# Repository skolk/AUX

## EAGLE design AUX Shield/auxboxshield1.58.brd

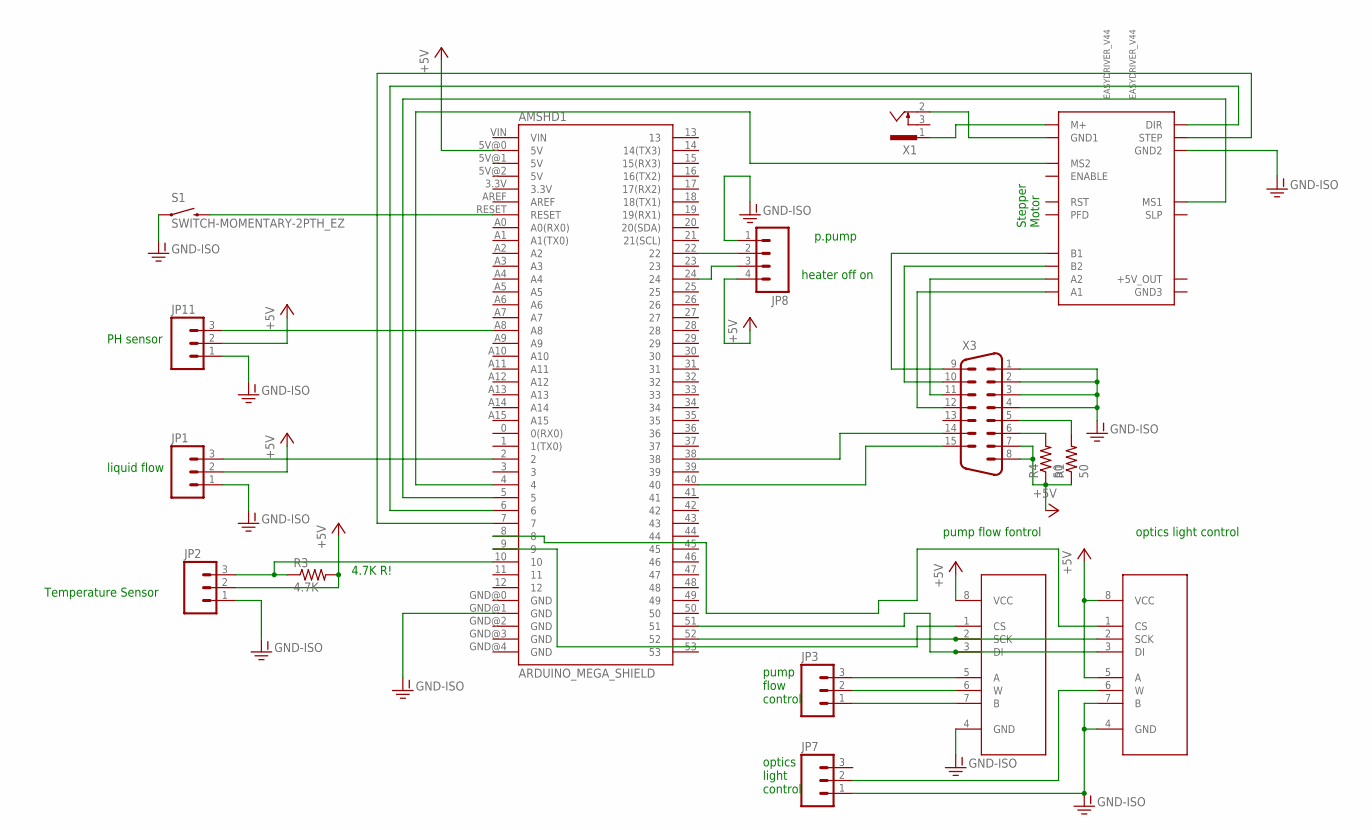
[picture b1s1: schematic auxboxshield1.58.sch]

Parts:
AMSHD1: ARDUINO_MEGA_SHIELD
EASYDRIVER_V44: EASYDRIVER_V44
JP1, JP2, JP3, JP7, JP11: M03POLAR; MOLEX-1X3
JP8: M04POLAR; MOLEX-1X4
R1, R4: 50; AXIAL-0.3
R3: 4.7K; AXIAL-0.3
S1: SWITCH-MOMENTARY-2PTH_EZ; TACTILE-PTH-EZ
U1, U2: MCP41XXXDIL; DIL-08
X1: SCD-014A; SCD-014-A
X3: M15V

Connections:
+5V: AMSHD1.5V@0 (5V), JP1.2, JP2.2, JP8.4, JP11.2, R1.P$1 (1), R3.P$2 (2), R4.P$1 (1), U1.5 (A), U1.8 (VCC), U2.8 (VCC), X3.7, X3.8
GND-ISO: AMSHD1.GND@1 (GND), EASYDRIVER_V44.GND2, JP1.1, JP2.1, JP7.1, JP8.1, JP11.1, S1.1, U1.4 (GND), U1.7 (B), U2.4 (GND), X3.1, X3.2, X3.3, X3.4
unnamed: EASYDRIVER_V44.M+, X1.1
unnamed: AMSHD1.38, X3.14
unnamed: R1.P$2 (2), X3.5
unnamed: EASYDRIVER_V44.GND1, X1.2
unnamed: EASYDRIVER_V44.A1, X3.12
unnamed: AMSHD1.RESET, S1.3 (2)
unnamed: EASYDRIVER_V44.A2, X3.11
unnamed: AMSHD1.9, U2.1 (CS)
unnamed: AMSHD1.5, EASYDRIVER_V44.MS1
unnamed: AMSHD1.22, JP8.2
unnamed: AMSHD1.A8, JP11.3
unnamed: AMSHD1.4, EASYDRIVER_V44.MS2
unnamed: AMSHD1.52, U1.2 (SCK), U2.2 (SCK)
unnamed: AMSHD1.24, JP8.3
unnamed: AMSHD1.40, X3.15
unnamed: AMSHD1.51, U1.3 (DI), U2.3 (DI)
unnamed: JP3.3, U2.5 (A)
unnamed: JP3.2, U2.6 (W)
unnamed: AMSHD1.10, JP2.3, R3.P$1 (1)
unnamed: EASYDRIVER_V44.B2, X3.10
unnamed: AMSHD1.2, JP1.3
unnamed: AMSHD1.6, EASYDRIVER_V44.DIR
unnamed: AMSHD1.7, EASYDRIVER_V44.STEP
unnamed: EASYDRIVER_V44.B1, X3.9
unnamed: JP3.1, U2.7 (B)
unnamed: R4.P$2 (2), X3.6
unnamed: AMSHD1.8, U1.1 (CS)
unnamed: JP7.2, U1.6 (W)

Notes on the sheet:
Stepper Motor
Temperature Sensor
liquid flow
PH sensor
4.7K R!
pump flow fontrol
optics light control
heater off on
p.pump
pump flow control
optics light control

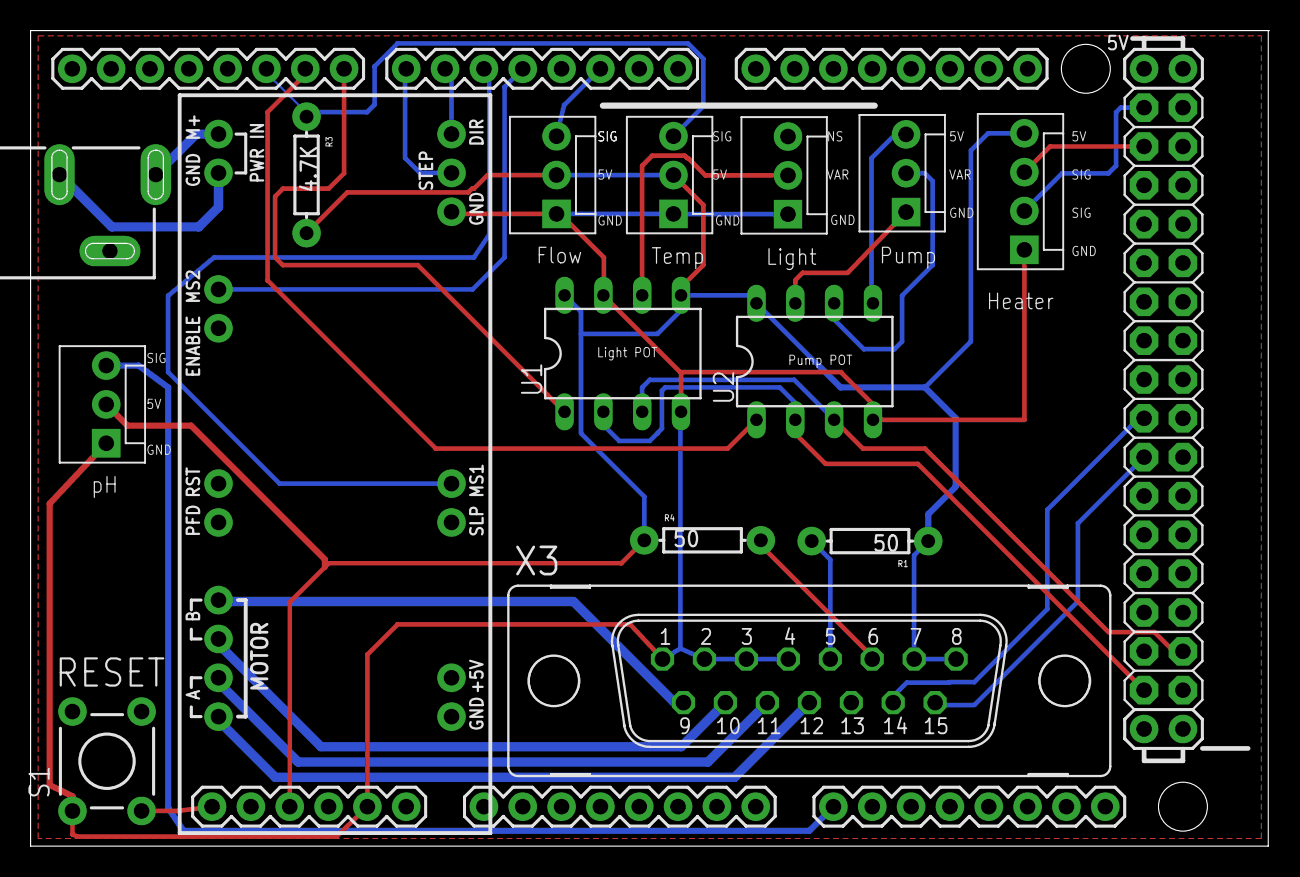
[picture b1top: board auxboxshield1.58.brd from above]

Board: 2 copper layers, 81.0 x 53.3 mm, 16 parts (0 on the bottom side), 30 nets.

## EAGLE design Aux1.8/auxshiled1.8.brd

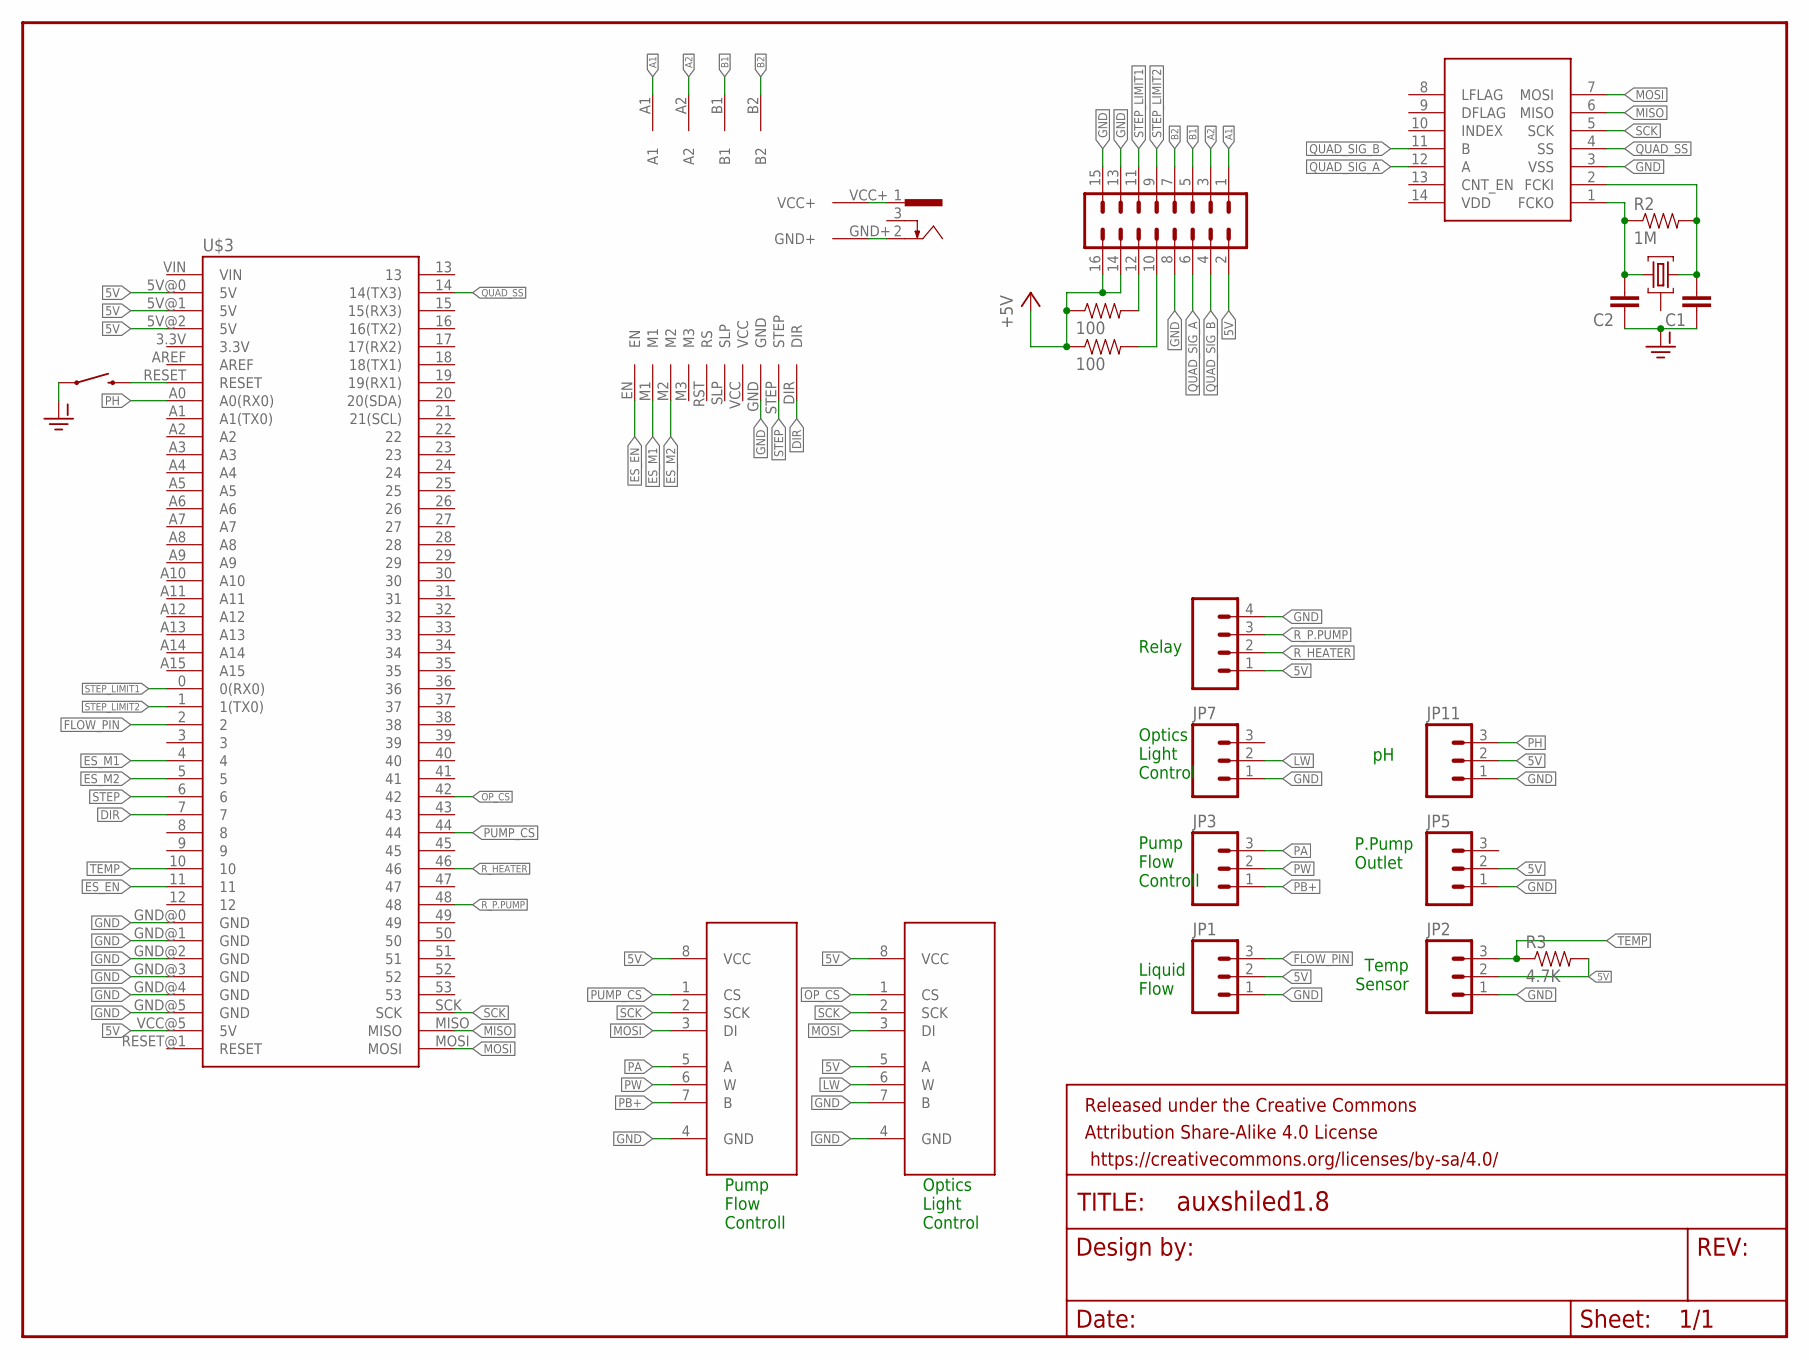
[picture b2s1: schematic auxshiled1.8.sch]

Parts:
C1, C2: 0.1UF-50V-20%(PTH)KIT-EZ; CAP-PTH-SMALL-KIT
FRAME1: FRAME-LETTER; CREATIVE_COMMONS
JP1, JP2, JP3, JP5, JP7, JP11: M03POLAR; MOLEX-1X3
PUMPDIGIPOT: MCP41XXXDIL; DIL-08
QF2: 14M20BHC49T; HC49U
R1, R4: 100; AXIAL-0.3
R2: 1M; AXIAL-0.3
R3: 4.7K; AXIAL-0.3
RELAY: M04POLAR; MOLEX-1X4
S1: SWITCH-MOMENTARY-2PTH_EZ; TACTILE-PTH-EZ
U1: MCP41XXXDIL; DIL-08
U$1: M08X2; 2X8
U$2: LS7366R; SO014
U$3: ARDUINO-MEGA-V2; ARDUINO_MEGA-PRO-5V
U$4: BIG_EASY_DRIVER; BIG_EASY_DRIVER_PACK
X1: SCD-014A; SCD-014-A

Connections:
5V: JP1.2, JP2.2, JP5.2, JP11.2, PUMPDIGIPOT.8 (VCC), R1.P$1 (1), R3.P$2 (2), R4.P$1 (1), RELAY.1, U1.5 (A), U1.8 (VCC), U$1.2, U$1.14, U$1.16, U$3.5V@0 (5V), U$3.5V@1 (5V), U$3.5V@2 (5V), U$3.VCC@5 (5V)
A1: U$1.1, U$4.A1
A2: U$1.3, U$4.A2
B1: U$1.5, U$4.B1
B2: U$1.7, U$4.B2
DIR: U$3.7, U$4.DIR
ES_EN: U$3.11, U$4.EN
ES_M1: U$3.4, U$4.M1
ES_M2: U$3.5, U$4.M2
FLOW_PIN: JP1.3, U$3.2
GND: C1.1, C2.1, JP1.1, JP2.1, JP5.1, JP7.1, JP11.1, PUMPDIGIPOT.4 (GND), RELAY.4, S1.1, U1.4 (GND), U1.7 (B), U$1.8, U$1.13, U$1.15, U$2.3 (VSS), U$3.GND@0 (GND), U$3.GND@1 (GND), U$3.GND@2 (GND), U$3.GND@3 (GND), U$3.GND@4 (GND), U$3.GND@5 (GND), U$4.GND
LW: JP7.2, U1.6 (W)
MISO: U$2.6 (MISO), U$3.MISO
MOSI: PUMPDIGIPOT.3 (DI), U1.3 (DI), U$2.7 (MOSI), U$3.MOSI
unnamed: U$4.VCC+, X1.1
unnamed: U$4.GND+, X1.2
unnamed: R1.P$2 (2), U$1.10
unnamed: S1.3 (2), U$3.RESET
unnamed: C1.2, QF2.3, R2.P$2 (2), U$2.2 (FCKI)
unnamed: C2.2, QF2.1, R2.P$1 (1), U$2.1 (FCKO)
unnamed: R4.P$2 (2), U$1.12
OP_CS: U1.1 (CS), U$3.42
PA: JP3.3, PUMPDIGIPOT.5 (A)
PB+: JP3.1, PUMPDIGIPOT.7 (B)
PH: JP11.3, U$3.A0 (A0(RX0))
PUMP_CS: PUMPDIGIPOT.1 (CS), U$3.44
PW: JP3.2, PUMPDIGIPOT.6 (W)
QUAD_SIG_A: U$1.6, U$2.12 (A)
QUAD_SIG_B: U$1.4, U$2.11 (B)
QUAD_SS: U$2.4 (SS), U$3.14 (14(TX3))
R_HEATER: RELAY.2, U$3.46
R_P.PUMP: RELAY.3, U$3.48
SCK: PUMPDIGIPOT.2 (SCK), U1.2 (SCK), U$2.5 (SCK), U$3.SCK
STEP: U$3.6, U$4.STEP
STEP_LIMIT1: U$1.11, U$3.0 (0(RX0))
STEP_LIMIT2: U$1.9, U$3.1 (1(TX0))
TEMP: JP2.3, R3.P$1 (1), U$3.10

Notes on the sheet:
Temp Sensor
Liquid Flow
Pump Flow Controll
Optics Light Control
Optics Light Control
P.Pump Outlet
Relay

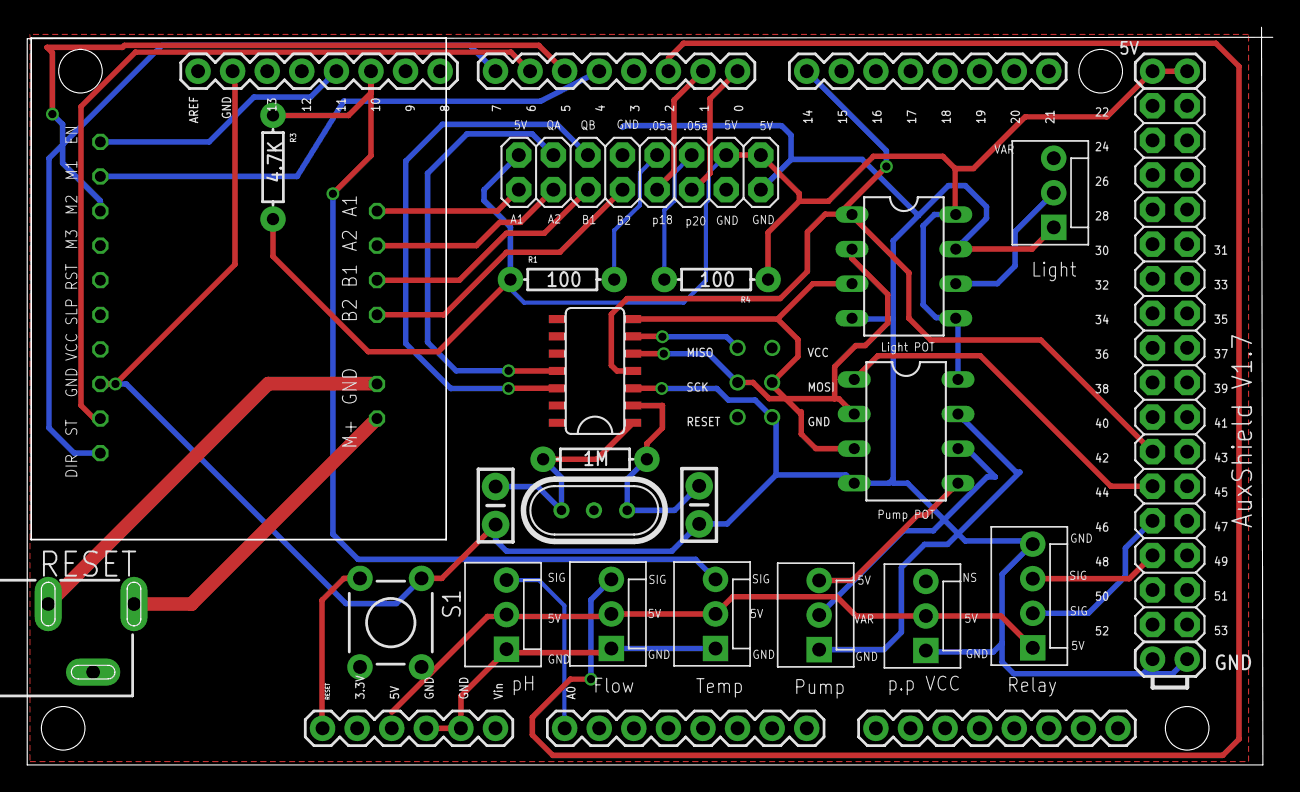
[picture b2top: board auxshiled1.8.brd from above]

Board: 2 copper layers, 91.3 x 54.1 mm, 23 parts (0 on the bottom side), 37 nets.

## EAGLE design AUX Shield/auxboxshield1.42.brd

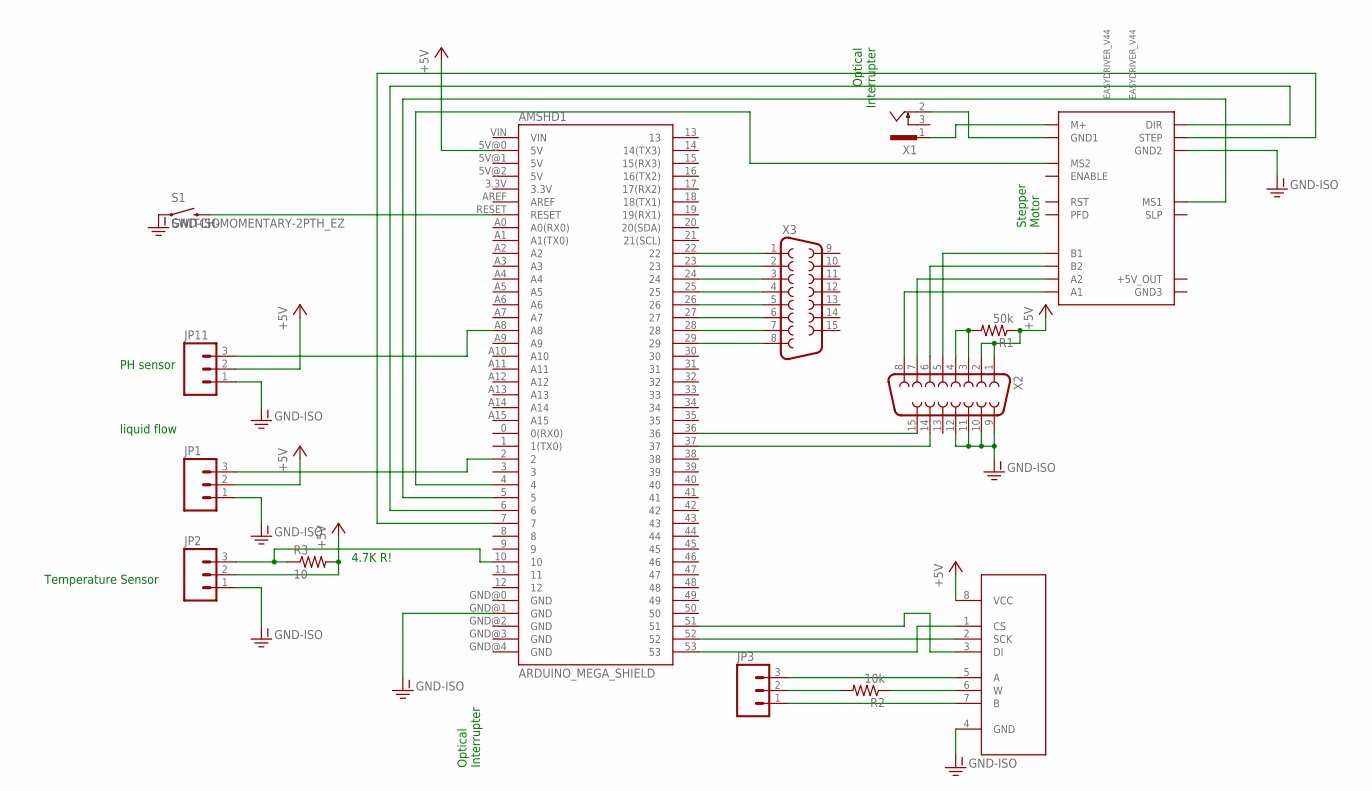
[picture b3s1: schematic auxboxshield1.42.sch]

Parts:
AMSHD1: ARDUINO_MEGA_SHIELD
EASYDRIVER_V44: EASYDRIVER_V44
JP1, JP2, JP3, JP11: M03POLAR; MOLEX-1X3
R1: 50k; AXIAL-0.3
R2: 10k; AXIAL-0.3
R3: 10; AXIAL-0.3
S1: SWITCH-MOMENTARY-2PTH_EZ; TACTILE-PTH-EZ
U2: MCP41XXXDIL; DIL-08
X1: SCD-014A; SCD-014-A
X2, X3: F15HP

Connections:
+5V: AMSHD1.5V@0 (5V), JP1.2, JP2.2, JP11.2, R1.P$1 (1), R3.P$2 (2), U2.8 (VCC), X2.1, X2.2
GND-ISO: AMSHD1.GND@1 (GND), EASYDRIVER_V44.GND2, JP1.1, JP2.1, JP11.1, S1.1, U2.4 (GND), X2.9, X2.10, X2.11, X2.12
unnamed: EASYDRIVER_V44.M+, X1.1
unnamed: EASYDRIVER_V44.A1, X2.8
unnamed: EASYDRIVER_V44.A2, X2.7
unnamed: R1.P$2 (2), X2.3, X2.4
unnamed: AMSHD1.22, X3.1
unnamed: EASYDRIVER_V44.GND1, X1.2
unnamed: EASYDRIVER_V44.B2, X2.6
unnamed: AMSHD1.23, X3.2
unnamed: AMSHD1.RESET, S1.3 (2)
unnamed: AMSHD1.24, X3.3
unnamed: EASYDRIVER_V44.B1, X2.5
unnamed: AMSHD1.53, U2.1 (CS)
unnamed: AMSHD1.5, EASYDRIVER_V44.MS1
unnamed: AMSHD1.25, X3.4
unnamed: AMSHD1.A8, JP11.3
unnamed: AMSHD1.4, EASYDRIVER_V44.MS2
unnamed: AMSHD1.52, U2.2 (SCK)
unnamed: AMSHD1.26, X3.5
unnamed: AMSHD1.27, X3.6
unnamed: AMSHD1.51, U2.3 (DI)
unnamed: JP3.3, U2.5 (A)
unnamed: AMSHD1.28, X3.7
unnamed: AMSHD1.29, X3.8
unnamed: R2.P$1 (1), U2.6 (W)
unnamed: JP3.2, R2.P$2 (2)
unnamed: AMSHD1.10, JP2.3, R3.P$1 (1)
unnamed: AMSHD1.2, JP1.3
unnamed: AMSHD1.6, EASYDRIVER_V44.DIR
unnamed: AMSHD1.7, EASYDRIVER_V44.STEP
unnamed: JP3.1, U2.7 (B)
unnamed: AMSHD1.36, X2.15
unnamed: AMSHD1.37, X2.14

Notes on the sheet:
Stepper Motor
Optical Interrupter
Temperature Sensor
liquid flow
PH sensor
4.7K R!

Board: 2 copper layers, 15 parts (0 on the bottom side), 34 nets, no tracks yet.

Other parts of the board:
DRILEGEND: DRILEGEND

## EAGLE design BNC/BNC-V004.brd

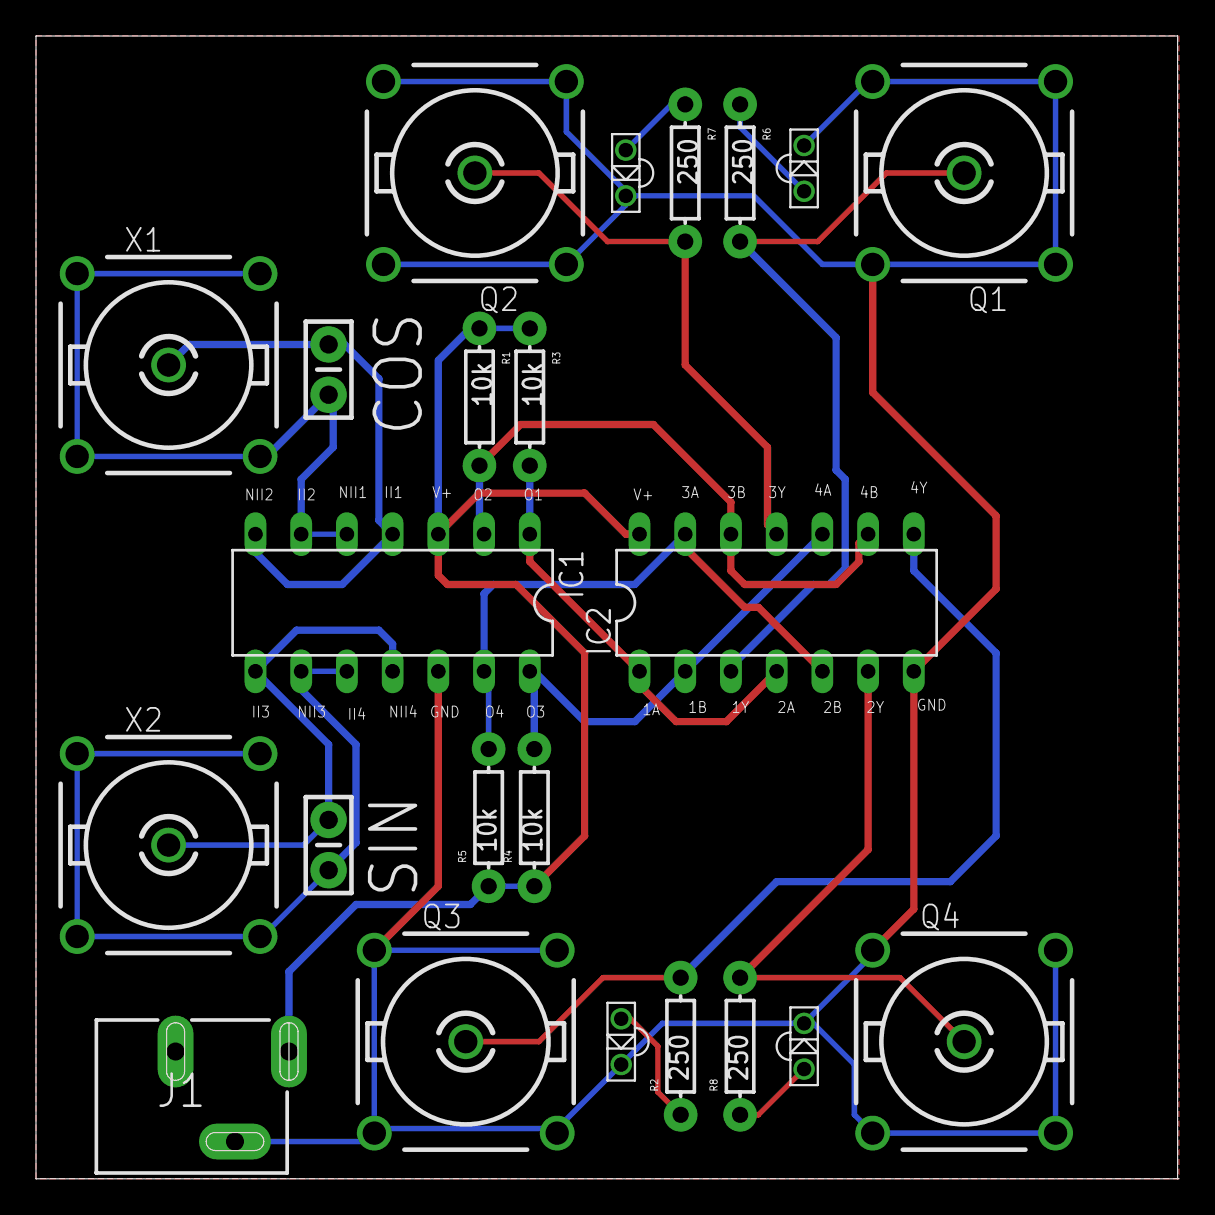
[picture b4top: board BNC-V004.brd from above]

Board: 2 copper layers, 63.5 x 63.5 mm, 23 parts (0 on the bottom side), 18 nets.

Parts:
C1, C3: CAP-PTH-SMALL-KIT
IAG2-D2, IAG3-D3, IAG4-D4: LTE-302
IAG-D1: LTE-302
IC1: LM339N; DIL14
IC2: 74AC08N; DIL14
J1: POWER_JACKSLT; POWER_JACK_SLOT
Q1, Q2, Q3, Q4: R141426
R1, R3, R4, R5: 10k; AXIAL-0.3
R2, R6, R7, R8: 250; AXIAL-0.3
X1, X2: R141426

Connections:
5V: IC1.3, IC2.14, J1.PWR, R1.P$1, R3.P$1, R4.P$1, R5.P$1
GND: IAG2-D2.C, IAG3-D3.C, IAG4-D4.C, IAG-D1.C, IC1.12, IC2.7, J1.GND@2, Q1.2, Q1.3, Q1.4, Q1.5, Q2.2, Q2.3, Q2.4, Q2.5, Q3.2, Q3.3, Q3.4, Q3.5, Q4.2, Q4.3, Q4.4, Q4.5
unnamed: IC1.2, IC2.9, IC2.12, R1.P$2
unnamed: IC2.11, Q2.1, R7.P$2
unnamed: IAG4-D4.A, R7.P$1
unnamed: IC1.1, IC2.1, IC2.4, R3.P$2
unnamed: IC1.14, IC2.2, IC2.10, R4.P$2
unnamed: IC1.13, IC2.5, IC2.13, R5.P$2
unnamed: C3.2, IC1.5, IC1.6, X1.2, X1.3, X1.4, X1.5
unnamed: C3.1, IC1.4, IC1.7, X1.1
unnamed: C1.1, IC1.8, IC1.11, X2.1
unnamed: C1.2, IC1.9, IC1.10, X2.2, X2.3, X2.4, X2.5
unnamed: IC2.8, Q3.1, R2.P$2
unnamed: IAG3-D3.A, R2.P$1
unnamed: IC2.6, Q4.1, R8.P$2
unnamed: IAG2-D2.A, R8.P$1
unnamed: IC2.3, Q1.1, R6.P$2
unnamed: IAG-D1.A, R6.P$1

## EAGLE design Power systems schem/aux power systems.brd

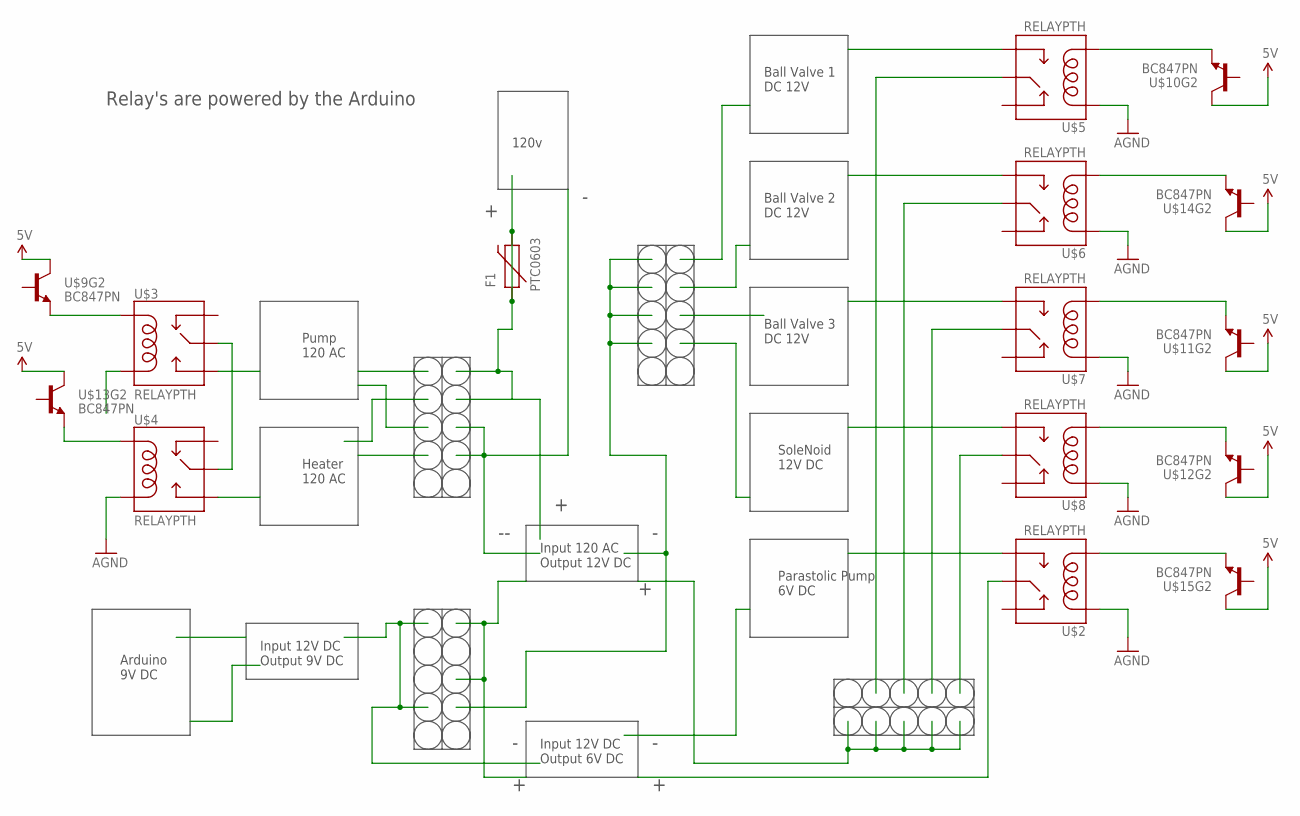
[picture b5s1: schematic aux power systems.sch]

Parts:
F1: PTC0603; 0603
U$2, U$3, U$4, U$5, U$6, U$7, U$8: RELAYPTH; RELAY-G5Q
U$9, U$10, U$11, U$12, U$13, U$14, U$15: BC847PN; SOT363

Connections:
5V: U$9.3 (C), U$10.3 (C), U$11.3 (C), U$12.3 (C), U$13.3 (C), U$14.3 (C), U$15.3 (C)
AGND: U$2.5 (COIL1), U$4.1 (COIL2), U$5.5 (COIL1), U$6.5 (COIL1), U$7.5 (COIL1), U$8.5 (COIL1)
B$2: U$2.3 (NO), U$3.3 (NO), U$4.3 (NO), U$5.3 (NO), U$6.3 (NO), U$7.3 (NO), U$8.3 (NO)
B$3: U$2.2 (MAIN), U$7.2 (MAIN)
unnamed: U$3.5 (COIL1), U$9.4 (E)
unnamed: U$4.5 (COIL1), U$13.4 (E)
unnamed: U$2.1 (COIL2), U$15.4 (E)
unnamed: U$8.1 (COIL2), U$12.4 (E)
unnamed: U$7.1 (COIL2), U$11.4 (E)
unnamed: U$6.1 (COIL2), U$14.4 (E)
unnamed: U$5.1 (COIL2), U$10.4 (E)
unnamed: U$3.2 (MAIN), U$4.2 (MAIN)
unnamed: F1.1, F1.2

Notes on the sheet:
Arduino 9V DC
SoleNoid 12V DC
Parastolic Pump 6V DC
Pump 120 AC
Heater 120 AC
Ball Valve 1 DC 12V
Ball Valve 2 DC 12V
Ball Valve 3 DC 12V
Input 120 AC Output 12V DC
Input 12V DC Output 9V DC
Input 12V DC Output 6V DC
120v
Relay's are powered by the Arduino

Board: 2 copper layers, 15 parts (0 on the bottom side), 13 nets, no tracks yet.

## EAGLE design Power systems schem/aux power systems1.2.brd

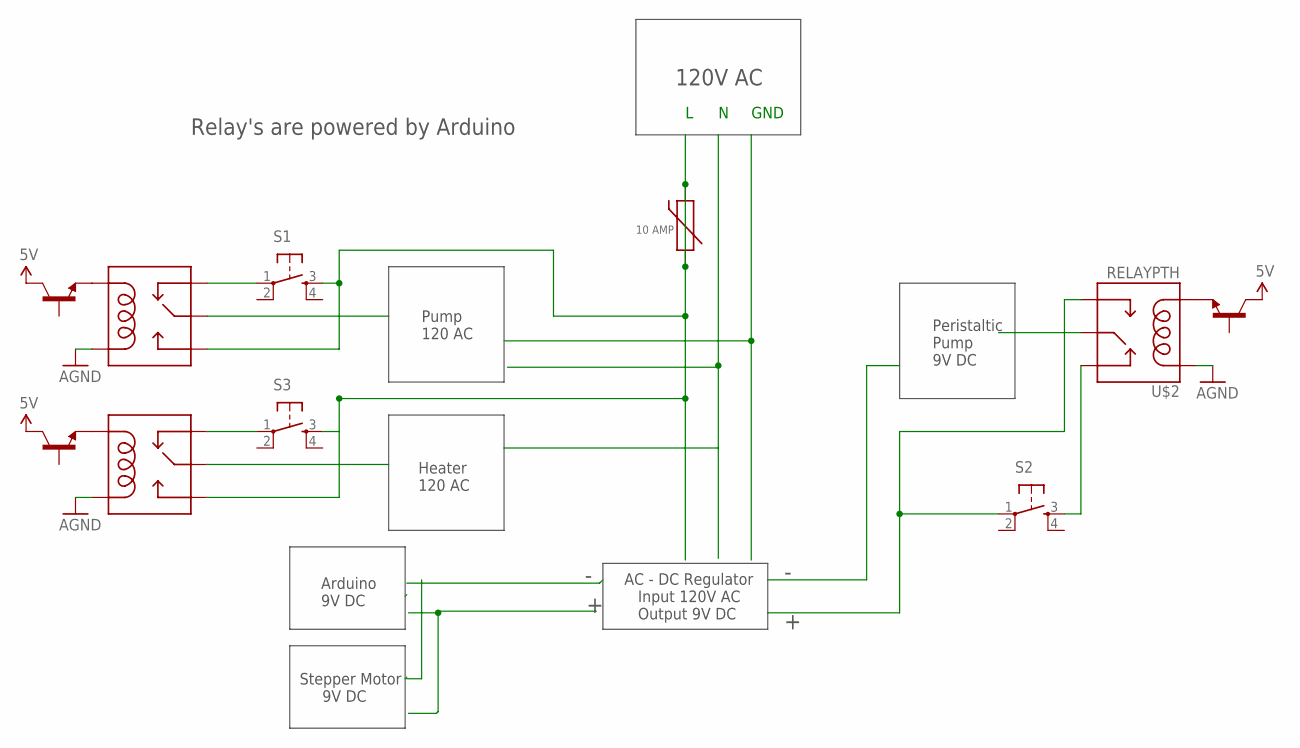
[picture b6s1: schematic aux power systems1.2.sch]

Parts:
F1: PTC0603; 0603
S1, S2, S3: TAC_SWITCHPTH; TACTILE-PTH
U$2, U$3, U$4: RELAYPTH; RELAY-G5Q
U$9, U$13, U$15: BC847PN; SOT363

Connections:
5V: U$9.3 (C), U$13.3 (C)
6V: U$15.3 (C)
AGND: U$2.5 (COIL1), U$3.1 (COIL2), U$4.1 (COIL2)
B$2: U$3.2 (MAIN), U$4.2 (MAIN)
B$3: S2.1, U$2.3 (NO)
unnamed: U$3.5 (COIL1), U$9.4 (E)
unnamed: U$4.5 (COIL1), U$13.4 (E)
unnamed: U$2.1 (COIL2), U$15.4 (E)
unnamed: S2.3, U$2.4 (NC)
unnamed: F1.1, F1.2, S1.3, S3.3, U$3.3 (NO), U$4.3 (NO)
unnamed: S3.1, U$4.4 (NC)
unnamed: S1.1, U$3.4 (NC)

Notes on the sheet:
Arduino 9V DC
Peristaltic Pump 9V DC
Pump 120 AC
Heater 120 AC
AC - DC Regulator Input 120V AC Output 9V DC
120V AC
Relay's are powered by Arduino
GND
10 AMP
Stepper Motor 9V DC

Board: 2 copper layers, 21 parts (0 on the bottom side), 11 nets, no tracks yet.

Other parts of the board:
120AC: SCREWTERMINAL-3.5MM-3
120ACSWITCH: M022.54MM_SCREWTERM; 1X02_2.54_SCREWTERM
HEATER: SCREWTERMINAL-3.5MM-3
HEATERSWITCH: M022.54MM_SCREWTERM; 1X02_2.54_SCREWTERM
J1: POWER_JACKSLT; POWER_JACK_SLOT
JP1: SCREWTERMINAL-3.5MM-3
JP4, JP6: M022.54MM_SCREWTERM; 1X02_2.54_SCREWTERM
JP10: 1X05
PARAPUMPSWICH: M022.54MM_SCREWTERM; 1X02_2.54_SCREWTERM
X1: F15H

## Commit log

2015-02-11 hello world
2016-01-13 yyyyyyyy enter the commit message for your changes. Lines starting

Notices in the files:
parts and their libraries:
SparkFun-Connectors: Licensing: Creative Commons ShareAlike 4.0 International - https://creativecommons.org/licenses/by-sa/4.0
SparkFun-Aesthetics: Released under the Creative Commons Attribution Share-Alike 4.0 License
SparkFun-Aesthetics: https://creativecommons.org/licenses/by-sa/4.0
